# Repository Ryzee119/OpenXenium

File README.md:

# OpenXenium

## About this Repository
This is an open source recreation of an Original Xbox LPC memory/IO device. Generally known as a *modchip*.
The VHDL is 100% compatible with XeniumOS, which is a legal non-Microsoft based bootloader made by TeamXodus for the Original Xbox. This allows loading user BIOS binaries and some basic Xbox tools (EEPROM Backup/modification, Hard drive Rebuilding, Locking, Unlocking, FTP access).  
  
The VHDL written by Team Xodus was never released and the CPLD is read protected so it is not trivial to extract the bitstream.
My own VHDL is probably quite similar to what Team Xodus produced for the Xenium Modchip but I have independently reverse engineered the behavioral design on the CPLD. (There was no bypassing of the protection features of a genuine Xenium.) Therefore I have named this project **OpenXenium**. *An open source recreation of the Xenium CPLD released under GPL which documents the internal workings by means of open source VHDL of the Xenium Modchip*.

I do a quick run through of the build process here: https://youtu.be/P6YYViKby74

To manage your OpenXenium device's flash memory, the Xenium-Tools homebrew program has been moved [here](https://github.com/Ryzee119/Xenium-Tools).

## Supported Features
The VHDL implements the following LPC transactions:
  * Memory Read/Writes (Translated to a parallel flash memory interface)
  * IO Read/Writes

From an Original Xbox perspective, this covers all requirements to make a custom LPC memory/IO peripheral for the console. Colloquially known as a *modchip* which can load custom BIOS files like Cromwell and its derivatives without modifying the onboard TSOP flash memory or softmodding. This supports IO control for accessories like LCD screens, LED controllers, external switches etc.

When used with XeniumOS the VHDL in this repo supports the following features:
  * Software controlled BIOS bank switching (any BIOS combinations that fit into 1mbyte of flash memory (4x256k, 1x512+2x256k, 2x512k, 1x1mbyte).
  * Instant boot to a chosen BIOS using the power button.
  * Boot the XeniumOS with eject button.
  * Ability to boot from the onboard BIOS (colloquially known as TSOP booting). This will completely disable OpenXenium and release D0/LFRAME(1.6) to boot the Xbox as if stock.
  * All the standard features in XeniumOS. (EEPROM tools, Hard drive tools, FTP/SMB Server etc.).
  * Three general purpose outputs. These are normally bitbanged as a SPI master (MOSI,CLK,CS) with the most common use an LCD, however could support any SPI peripheral in theory.
  * Two general purpose inputs. On a Xenium, these are I believe intended to be MISO lines to complement the SPI interface but could be used for any 3.3V digital logic.  
  * Three outputs are connected to an RGB led (Or an external user added RGB led).
  * Reserved memory on the flash chip for non-volatile storage of an EEPROM backup and XeniumOS settings.
  * If you bridge the two recovery pins on power up, it will attempt to boot the XeniumOS recovery BIOS if available. This functions the same as a genuine Xenium modchip.
  * I also simulate the LFRAME abort mechanism (*Ref Intel LPC Interface Spec Rev 1.1 Section 4.2.1.13*) so that this will work on a v1.6 Original Xbox. This aborts the LPC transaction to prevent the Xyclops responding to the MCPX LPC Memory Read requests during boot (and conflicting with an external LPC memory peripheral). This is generally accepted to be better than shorting LFRAME the ground constantly which some traditional *Modchips* do.

## XeniumOS BIOS
**The recommended way to get a copy of XeniumOS is to take a backup of your own Xenium modchip using [Xenium-Tools](https://github.com/Ryzee119/Xenium-Tools/releases).** It is also possible to parse the v2.3.1 XeniumOS update files released by Team Xodus to extract the neccessary data; however this will not contain the factory programmed recovery sector, but otherwise works in the same way.

This has been tested with XeniumOS 2.3.1 (Last release) and XeniumOS 2.3.1(Gold variant). The only way to obtain Gold OS is to dump the flash contents of your XeniumGold as the binary files were never distributed individually.

## Installation and Initial Setup
See [Installation.MD](https://github.com/Ryzee119/OpenXenium/blob/master/INSTALLATION.md)
## Licensing
OpenXenium is free and open source. Please respect the licenses available in their respective folders.
  *  Hardware is shared under the [CERN OHL version 1.2.](https://ohwr.org/cernohl).
  *  Firmware is shared under [GPLv3](https://www.gnu.org/licenses/quick-guide-gplv3.en.html).
  *  xenium-tools was made with [NXDK](https://github.com/XboxDev/nxdk) and is shared under [GPLv2](https://www.gnu.org/licenses/old-licenses/gpl-2.0.en.html).
## References that helped me in this project
  * [Intel LPC Spec](https://www.intel.com/content/dam/www/program/design/us/en/documents/low-pin-count-interface-specification.pdf)
  *  [NXDK](https://github.com/XboxDev/nxdk)  
  * [AladdinLCD  Github Repo (CPLD LCD Driver)](https://github.com/Ryzee119/AladdinLCD)
  * [LPC Analyser Plugin](https://github.com/Ryzee119/LPCAnalyzer)  
  * [Deconstructing the Xbox Boot ROM](https://mborgerson.com/deconstructing-the-xbox-boot-rom/)

If you like my work please consider a small donation<br>
<br>
By Ryzee119

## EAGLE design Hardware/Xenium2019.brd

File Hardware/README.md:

# OpenXenium PCB.
* This board was designed using [Autodesk Eagle](https://www.autodesk.com/products/eagle/overview). You can edit the `.brd` and `.sch` with this program.
* You can easily order the PCB and components (DIY soldering) via KitSpace: https://kitspace.org/boards/github.com/ryzee119/openxenium/.

## Schematic and Gerbers
See [Releases](https://github.com/Ryzee119/OpenXenium/releases).

## Bill of Materials
See [bom.csv](../.kitspace/bom.csv).

## High Res Assembled Photo

By Ryzee119

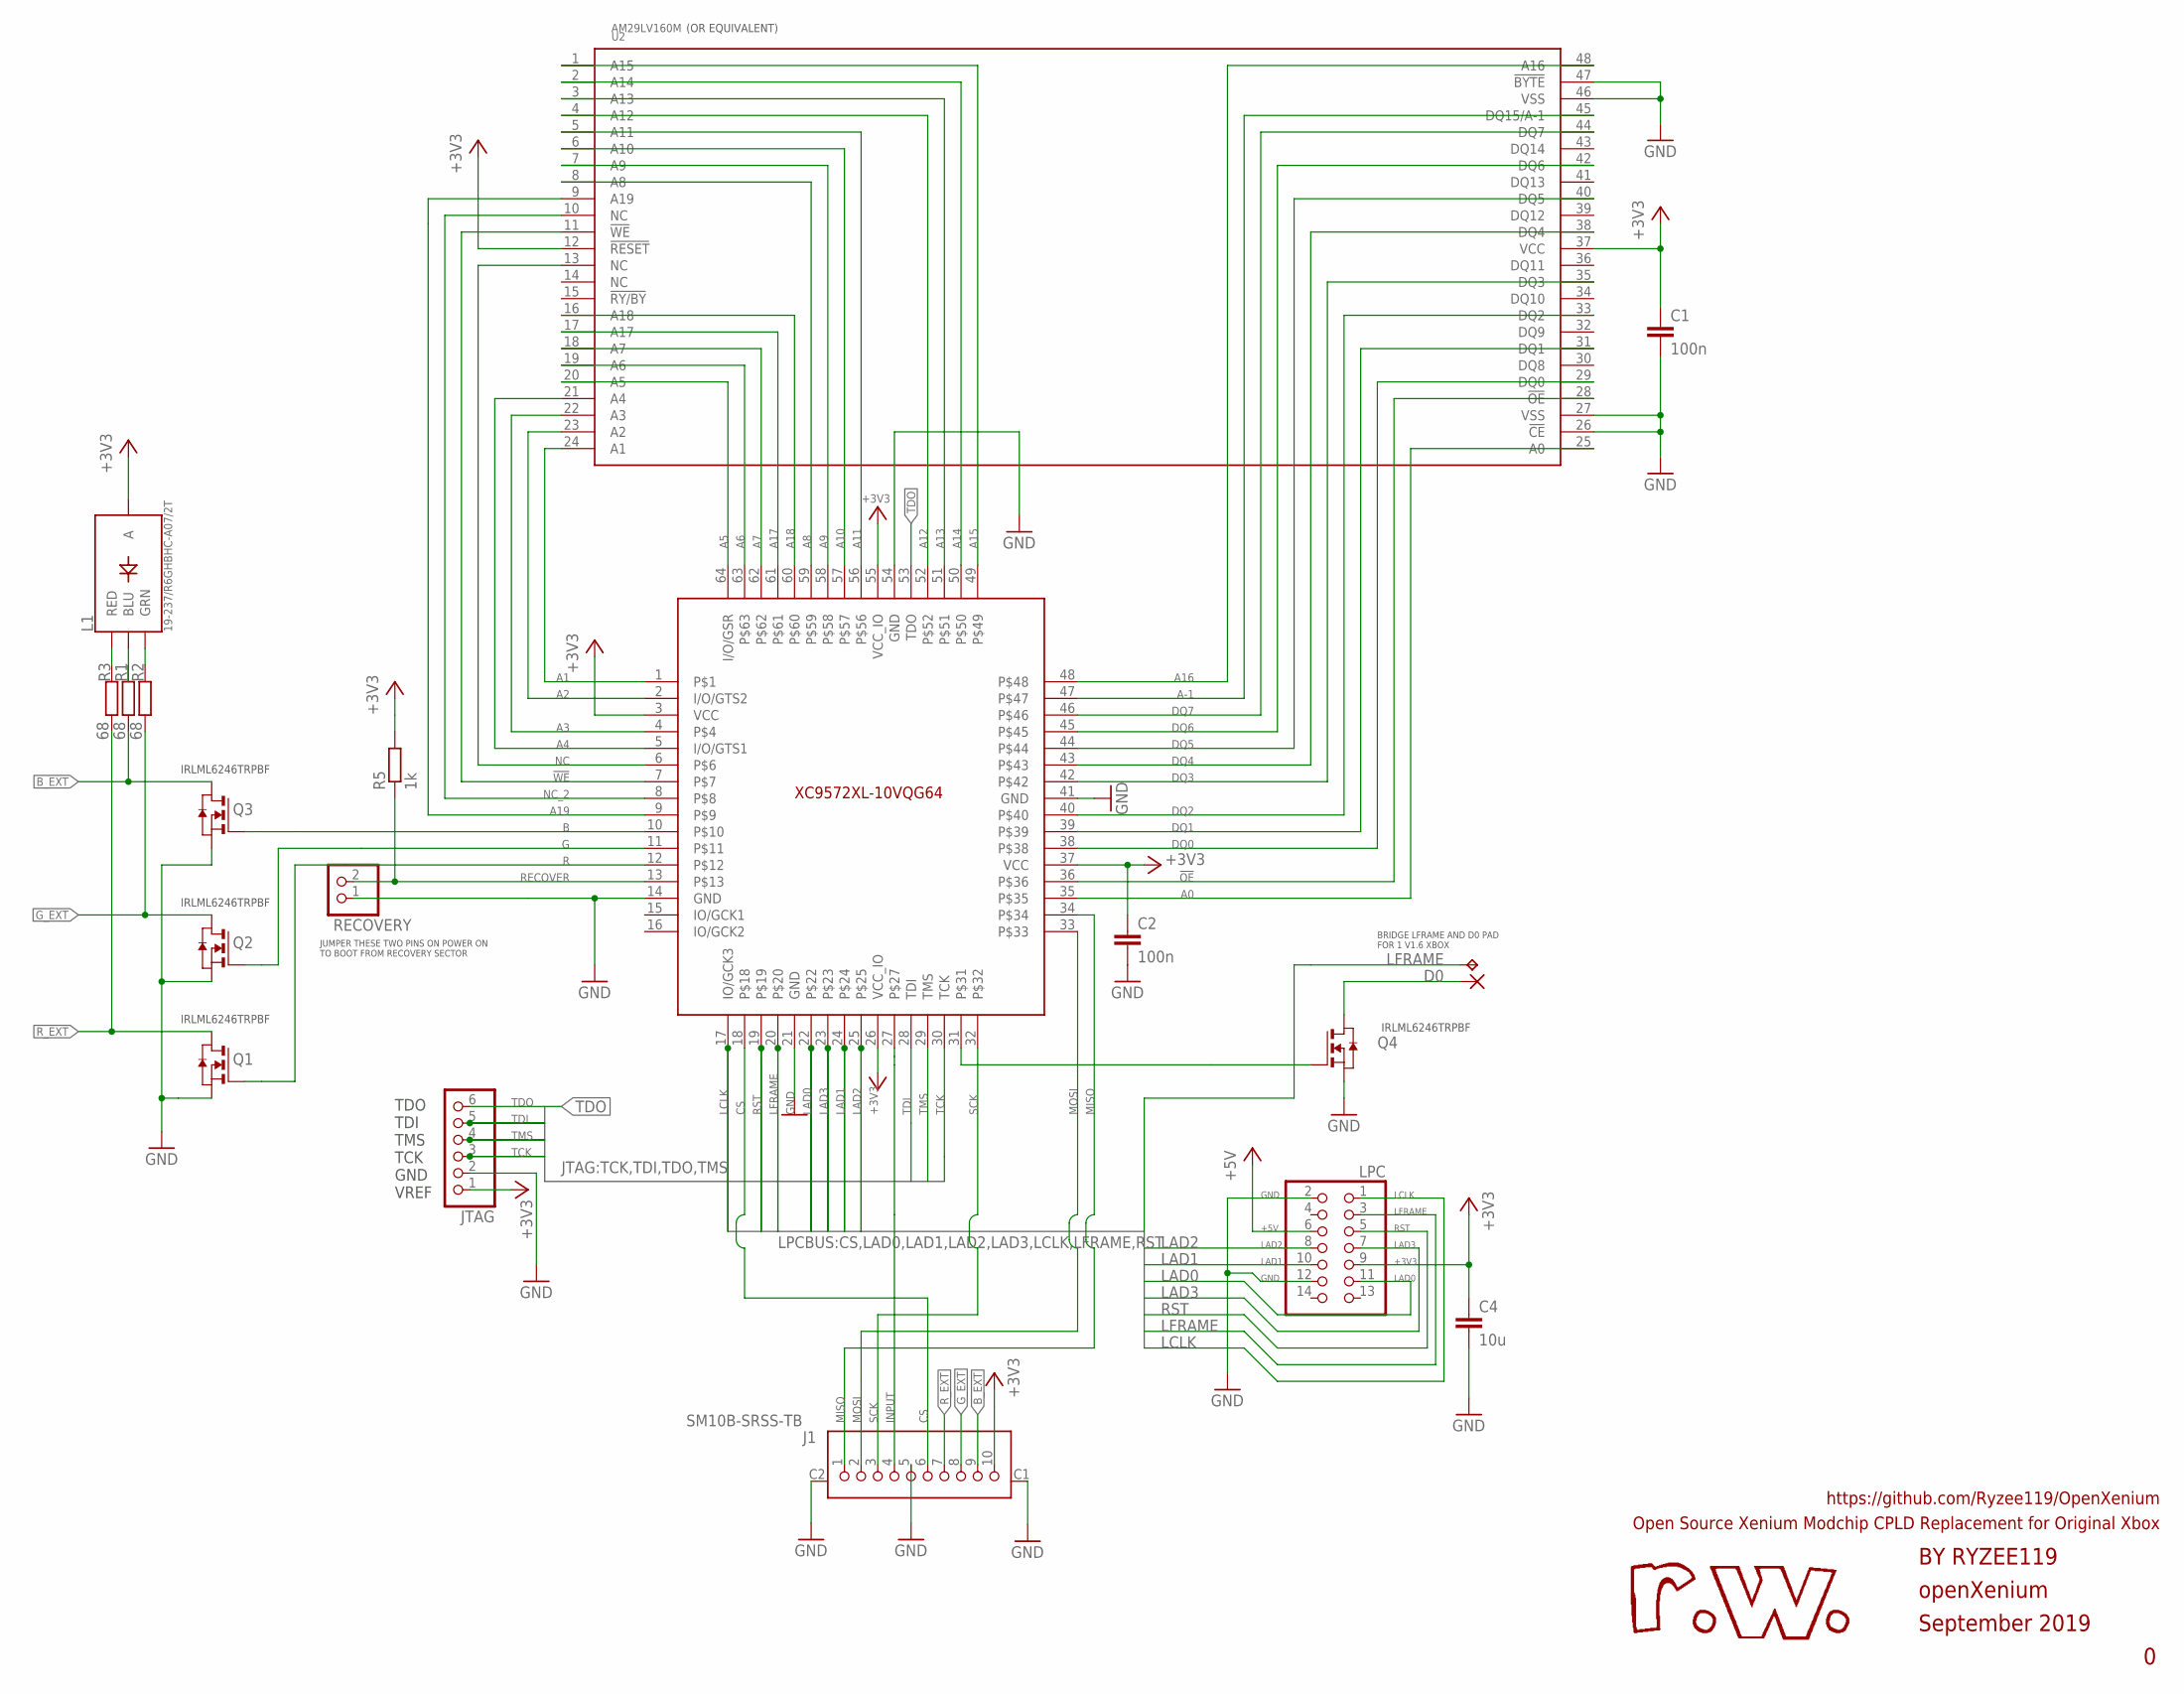
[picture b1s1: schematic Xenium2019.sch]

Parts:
C1, C2: 100n; C0603
C4: 10u; C0603
D0: SMD2; SMD1,27-2,54
J1: SM10B-SRSS-TB
JTAG: PINHD-1X6; 1X06
L1: 19-237/R6GHBHC-A07/2T; 4-SMD-R6GHBHC
LPC: PINHD-2X7; 2X07
Q1, Q2, Q3, Q4: 310mA/60V/1.6Ω; SOT-23
R1, R2, R3: 68; R0603
R5: 1k; R0603
RECOVERY: PINHD-1X2; 1X02
TP1: TPTP13SQ; TP13SQ
U1: XC9572XL-10VQG64; LQFP64
U2: AM29LV160M; TSOP48

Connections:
!OE: U1.36, U2.28 (!OE)
!WE: U1.7, U2.11 (!WE)
+3V3: C1.1, C2.1, C4.1, J1.10, JTAG.1, L1.P$2 (A), LPC.9, R5.2, U1.3 (VCC), U1.26 (VCC_IO), U1.37 (VCC), U1.55 (VCC_IO), U2.12 (!RESET), U2.37 (VCC)
+5V: LPC.6
A0: U1.35, U2.25 (A0)
A1: U1.1, U2.24 (A1)
A2: U1.2 (I/O/GTS2), U2.23 (A2)
A3: U1.4, U2.22 (A3)
A4: U1.5 (I/O/GTS1), U2.21 (A4)
A5: U1.64 (I/O/GSR), U2.20 (A5)
A6: U1.63, U2.19 (A6)
A7: U1.62, U2.18 (A7)
A8: U1.59, U2.8 (A8)
A9: U1.58, U2.7 (A9)
A10: U1.57, U2.6 (A10)
A11: U1.56, U2.5 (A11)
A12: U1.52, U2.4 (A12)
A13: U1.51, U2.3 (A13)
A14: U1.50, U2.2 (A14)
A15: U1.49, U2.1 (A15)
A16: U1.48, U2.48 (A16)
A17: U1.61, U2.17 (A17)
A18: U1.60, U2.16 (A18)
A19: U1.9, U2.9 (A19)
A-1: U1.47, U2.45 (DQ15/A-1)
B: Q3.3 (G), U1.10
BLUE: L1.P$4 (BLU), R1.1
B_EXT: J1.9, Q3.1 (D), R1.2
CS: J1.6, U1.18
DQ0: U1.38, U2.29 (DQ0)
DQ1: U1.39, U2.31 (DQ1)
DQ2: U1.40, U2.33 (DQ2)
DQ3: U1.42, U2.35 (DQ3)
DQ4: U1.43, U2.38 (DQ4)
DQ5: U1.44, U2.40 (DQ5)
DQ6: U1.45, U2.42 (DQ6)
DQ7: U1.46, U2.44 (DQ7)
G: Q2.3 (G), U1.11
GND: C1.2, C2.2, C4.2, J1.5, J1.C1 (MNT2), J1.C2 (MNT1), JTAG.2, LPC.2, LPC.12, Q1.2 (S), Q2.2 (S), Q3.2 (S), Q4.2 (S), RECOVERY.1, U1.14 (GND), U1.21 (GND), U1.41 (GND), U1.54 (GND), U2.26 (!CE), U2.27 (VSS), U2.46 (VSS), U2.47 (!BYTE)
GREEN: L1.P$3 (GRN), R2.1
G_EXT: J1.8, Q2.1 (D), R2.2
INPUT: J1.4, U1.27
LAD0: LPC.11, U1.22
LAD1: LPC.10, U1.24
LAD2: LPC.8, U1.25
LAD3: LPC.7, U1.23
LCLK: LPC.1, U1.17 (IO/GCK3)
LFRAME: LPC.3, TP1.TP, U1.20
MISO: J1.1, U1.34
MOSI: J1.2, U1.33
unnamed: Q4.3 (G), U1.31
unnamed: D0.1, Q4.1 (D)
NC: U1.6, U2.13 (NC)
NC_2: U1.8, U2.10 (NC)
R: Q1.3 (G), U1.12
RECOVER: R5.1, RECOVERY.2, U1.13
RED: L1.P$1 (RED), R3.1
RST: LPC.5, U1.19
R_EXT: J1.7, Q1.1 (D), R3.2
SCK: J1.3, U1.32
TCK: JTAG.3, U1.30 (TCK)
TDI: JTAG.5, U1.28 (TDI)
TDO: JTAG.6, U1.53 (TDO)
TMS: JTAG.4, U1.29 (TMS)

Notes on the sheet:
TDO TDI TMS TCK GND VREF
openXenium
September 2019
BY RYZEE119
Open Source Xenium Modchip CPLD Replacement for Original Xbox
https://github.com/Ryzee119/OpenXenium
BRIDGE LFRAME AND D0 PAD FOR 1 V1.6 XBOX
JUMPER THESE TWO PINS ON POWER ON TO BOOT FROM RECOVERY SECTOR
IRLML6246TRPBF
(OR EQUIVALENT)

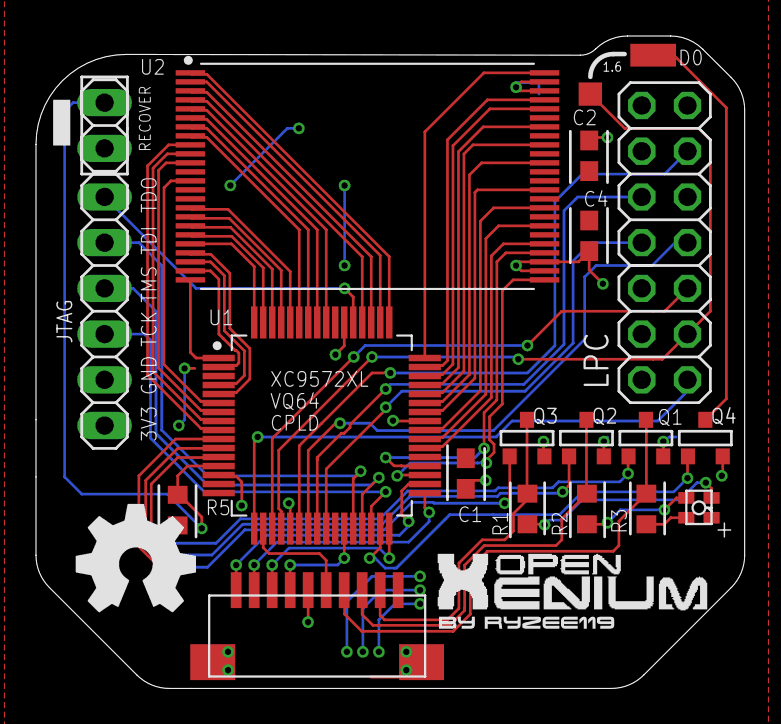
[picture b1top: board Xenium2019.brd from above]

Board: 2 copper layers, 39.4 x 36.2 mm, 20 parts (0 on the bottom side), 63 nets.

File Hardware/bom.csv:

Index,Quantity,Digikey,Manufacturer Part Number,Description
1,1,S7075-ND,PPTC072LFBN-RC,CONN HDR 14POS 0.1 TIN PCB
2,5,IRLML6246TRPBFCT-ND,IRLML6246TRPBF,MOSFET N-CH 20V 4.1A SOT-23
3,10,2019-RK73B1JTTD680JCT-ND,RK73B1JTTD680J,RES 68 OHM 5% 1/8W 0603
4,10,RMCF0603JJ1K00CT-ND,RMCF0603JJ1K00,RES 1K OHM 5% 1/10W 0603
5,1,1274-1013-ND,S29AL016J70TFI010,IC FLASH 16M PARALLEL 48TSOP
6,10,587-5869-1-ND,JMK107ABJ106MA-T,CAP CER 10UF 6.3V X5R 0603
7,1,122-1388-ND,XC9572XL-10VQG64C,IC CPLD 72MC 10NS 64VQFP
8,10,1276-1000-1-ND,CL10B104KB8NNNC,CAP CER 0.1UF 50V X7R 0603
9,1,1080-1590-1-ND,19-237/R6GHBHC-A07/2T,LED RGB CLEAR 4SMD
10,1,455-1810-1-ND,SM10B-SRSS-TB(LF)(SN),CONN HEADER SMD R/A 10POS 1MM

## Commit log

2019-11-08 Fixed CPLD recovery logic edge case
2019-11-08 Fixed recovery logic edge case for CPLD
2019-11-26 Updated URL to ISE Design Suite 14.7
2019-12-07 Rename MakeFile to Makefile
2019-12-12 Updated installation guide for clarity
2020-02-09 Add support for LPC peripherals (SuperIO etc.) at the expense of ripping out all LED/SPI functionality due to size constraints; additional testing/cleanup still needed
2020-02-09 Add back LED functionality
2020-02-12 Restore remaining features with a little optimization; had to enable exhaustive fit mode
2020-02-12 Forgot this
2020-02-19 Fix memory write bug and clean up whitespace
2020-05-01 Change paths to absolute
2020-05-14 Updated debugprints for better readability, cleaned up flash driver
2020-05-15 Updated skin.cfg definitions
2020-05-15 Some spelling issues
2020-05-25 Kitspace
2020-06-26 Updated Xilinx ISE instructions
2020-06-28 buffer IO writes
2020-06-29 tsop recovery
2020-06-29 A17->A15 typo
2020-08-10 Buffer all IO
2020-08-21 Rename file
2020-08-22 Add kitspace support
2020-08-24 Fix bom path in kitspace.yaml
2020-08-25 Add kitspace link
2021-01-11 Xtools: Migrate to new XeniumTools
2021-01-21 Bom: Add some spares
2021-01-30 HW: Cleanup readme and link schematic
2021-09-18 Add LPC Peripheral Support
    Prevents openxenium from blocking all other IO reads/writes. This enables other devices to be on the LPC bus at the same time.
    Particularly SuperIO debug modules.
2022-07-03 Fixed SuperIO compatability issues
2022-07-03 Whitespace fixes for VHDL code
2023-08-01 Optimize LPC logic for modern chips. Fixes XBlast OS on 1.0 (#6)
2023-08-01 Corrects README.md typo on LPC Aport Mechanism reference (fixes #28)
